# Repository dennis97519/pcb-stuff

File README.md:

# pcb-stuff
collection of small PCB projects

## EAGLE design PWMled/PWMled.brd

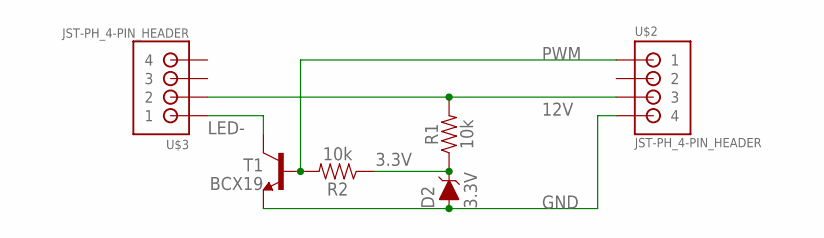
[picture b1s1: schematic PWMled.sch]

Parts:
D2: 3.3V; SOD-323
R1, R2: 10k; 0603
T1: BCX19; SOT23
U$2, U$3: JST-PH_4-PIN_HEADER; JST_B4B-PH_HEADER

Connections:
3.3V: D2.C, R1.1, R2.1
12V: R1.2, U$2.P3 (3), U$3.P2 (2)
GND: D2.A, T1.2 (E), U$2.P4 (4)
LED-: T1.3 (C), U$3.P1 (1)
PWM: R2.2, T1.1 (B), U$2.P1 (1)

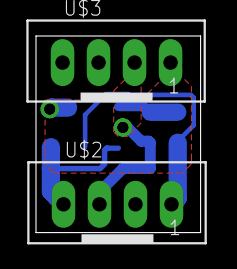
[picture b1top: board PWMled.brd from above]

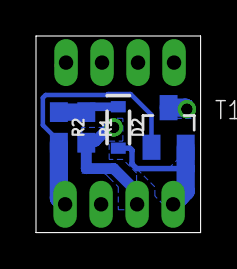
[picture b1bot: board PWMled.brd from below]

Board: 2 copper layers, 9.1 x 10.9 mm, 6 parts (4 on the bottom side), 5 nets.

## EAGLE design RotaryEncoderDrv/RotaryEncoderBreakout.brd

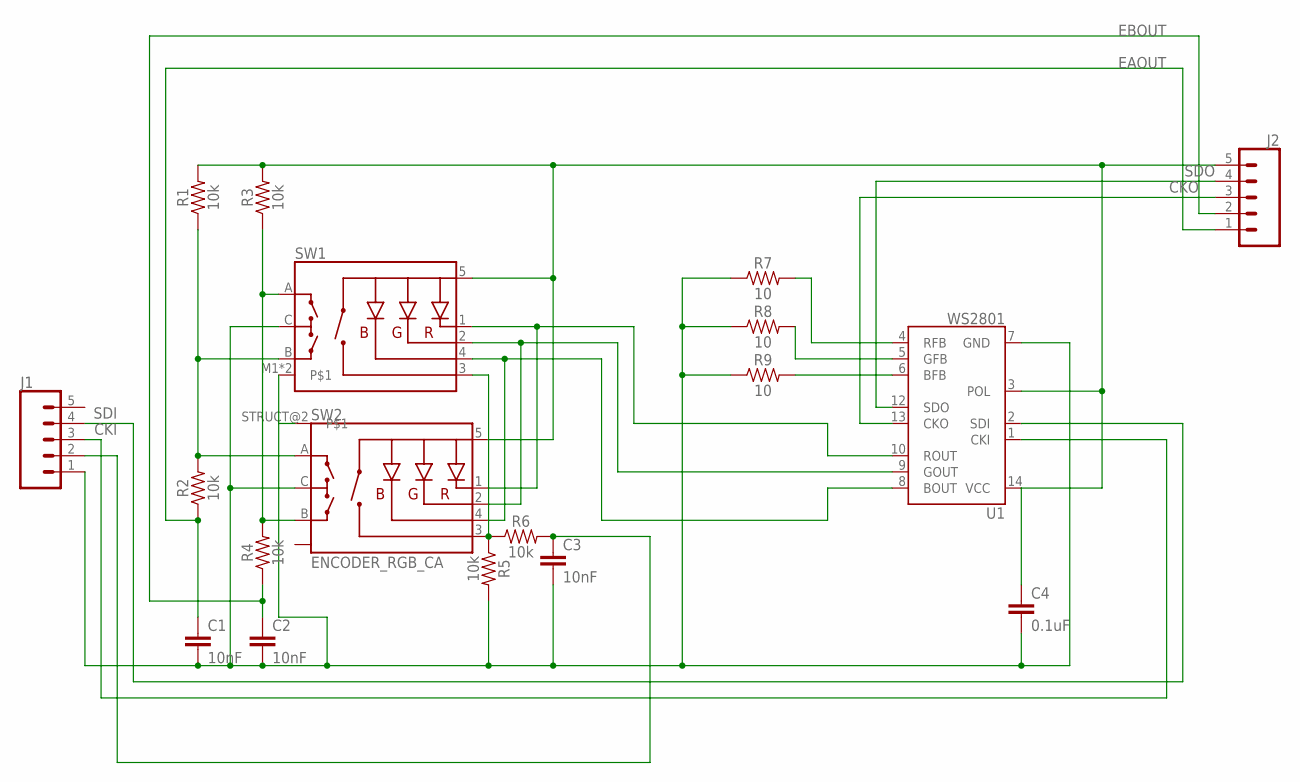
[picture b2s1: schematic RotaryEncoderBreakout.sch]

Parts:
C1, C2, C3: 10nF; 0603
C4: 0.1uF; 0603
J1, J2: CONN_05; 1X05
R1, R2, R3, R4, R5, R6: 10k; 0603
R7, R8, R9: 10; 0603
SW1: ENCODER_RGB_CA; ENCODER_LED_3
SW2: ENCODER_RGB_CA; EC12PSD-020
U1: WS2801; SOP-14

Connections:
A: R1.1, R2.2, SW1.B, SW2.A
B: R3.1, R4.2, SW1.A, SW2.B
BFB: R9.2, U1.6 (BFB)
BOUT: SW1.4 (-B), SW2.4 (-B), U1.8 (BOUT)
CKI: J1.3, U1.1 (CKI)
CKO: J2.3, U1.13 (CKO)
EAOUT: C1.1, J2.1, R2.1
EBOUT: C2.1, J2.2, R4.1
GFB: R8.2, U1.5 (GFB)
GND: C1.2, C2.2, C3.2, C4.2, J1.1, R5.2, R7.1, R8.1, R9.1, SW1.C, SW1.M1, SW1.M2, SW2.C, SW2.STRUCT@2, U1.7 (GND)
GOUT: SW1.2 (-G), SW2.2 (-G), U1.9 (GOUT)
RFB: R7.2, U1.4 (RFB)
ROUT: SW1.1 (-R), SW2.1 (-R), U1.10 (ROUT)
SDI: J1.4, U1.2 (SDI)
SDO: J2.4, U1.12 (SDO)
SW: R5.1, R6.2, SW1.3 (SW), SW2.3 (SW)
SWO: C3.1, J1.2, R6.1
VCC: C4.1, J2.5, R1.2, R3.2, SW1.5 (+), SW2.5 (+), U1.3 (POL), U1.14 (VCC)

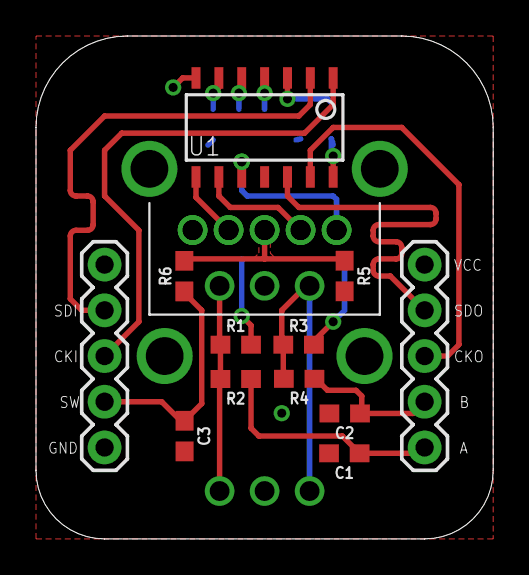
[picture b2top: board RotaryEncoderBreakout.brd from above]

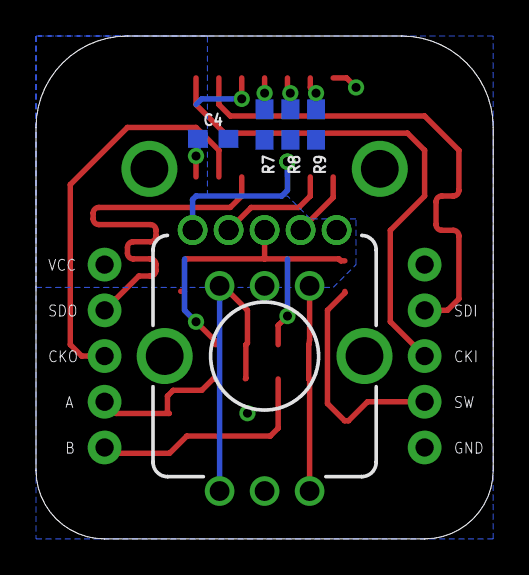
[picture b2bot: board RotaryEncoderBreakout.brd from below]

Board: 2 copper layers, 25.4 x 27.9 mm, 18 parts (5 on the bottom side), 18 nets.

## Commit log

2018-04-25 some cleanup
2018-04-25 more cleanup

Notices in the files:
parts and their libraries:
NXP_60_26022015: This library may be distributed and adapted freely for any purpose, as long as NXP is credited and any new creation is licensed under the same terms.
SparkFun-Resistors: Licensing: Creative Commons ShareAlike 4.0 International - https://creativecommons.org/licenses/by-sa/4.0
